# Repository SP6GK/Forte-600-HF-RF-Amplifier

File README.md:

# Forte 600

This is a hardware repository for a 600 W linear RF amplifier working in the 1.8-30 MHz spectrum. I have performed extensive measurements of the output for different configurations of the output transmission line transformers (TLTs). Unfortunately, I don't have the equipment to test this amplifier above 30 MHz, but according to S11 measurements of the output, it should also cover the 6 m band with lower output power.

I recommend using a single 17 Ohm coaxial cable (HF141-17-FEP by Qaxial) for winding the TLTs. However, as shown in my tests, you can use a parallel combination of 50 and 25 Ohm cables, which are easier to find and less expensive. Such an improvised transformer will have worse Power Added Efficiency (PAE) and won't maintain peak power over the maximum wide bandwidth. The ferrite cores used are Fair-Rite 2661102002.

For more details, you can read my paper or full master thesis, which will be published on my webpage in the coming months: [https://www.sp6gk.com/](https://www.sp6gk.com/).

This project was inspired by Razvan Fatu's 600 W amplifier: [A 600W Broadband HF Amplifier Using Affordable LDMOS Devices](https://qrpblog.com/2019/10/a-600w-broadband-hf-amplifier-using-affordable-ldmos-devices/). The goal of this work was to perform measurements of return loss of the input and output matching network, characterize the linearity, power added efficiency (PAE), and most importantly, the impact of "improvised" TLTs over a "textbook" TLT.

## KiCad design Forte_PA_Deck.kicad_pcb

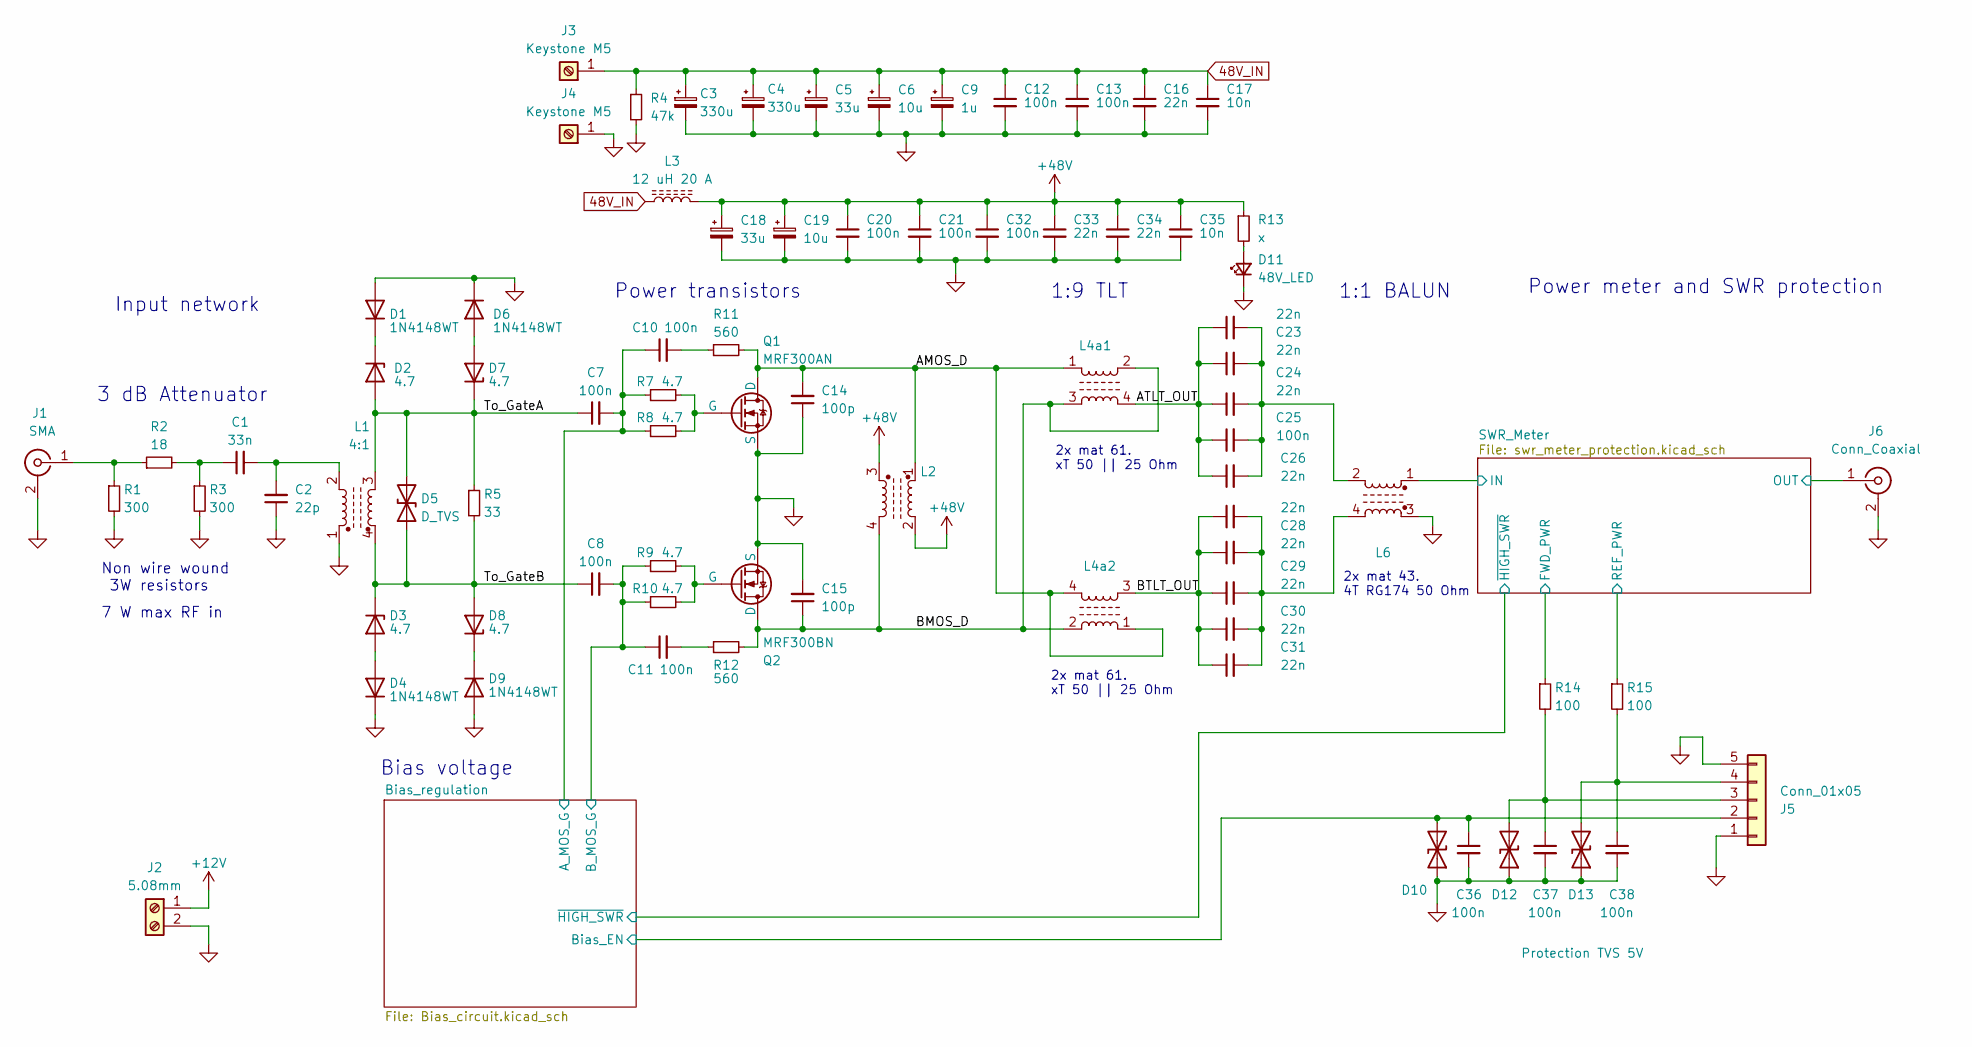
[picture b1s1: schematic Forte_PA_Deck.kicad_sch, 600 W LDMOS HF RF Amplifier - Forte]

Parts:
C1: 33n; C_0805_2012Metric_Pad1.18x1.45mm_HandSolder
C2: 22p; C_0805_2012Metric_Pad1.18x1.45mm_HandSolder
C3, C4: 330u; CP_Elec_18x17.5
C5, C18: 33u; CP_Elec_10x10.5
C6, C19: 10u; CP_Elec_10x10.5
C7, C8: 100n; C_1210_3225Metric_Pad1.33x2.70mm_HandSolder
C9: 1u; C_1206_3216Metric_Pad1.33x1.80mm_HandSolder
C10, C11, C12, C13, C20, C21, C25, C32: 100n; C_1206_3216Metric_Pad1.33x1.80mm_HandSolder
C14, C15: 100p; C_1206_3216Metric_Pad1.33x1.80mm_HandSolder
C16, C22, C23, C24, C26, C27, C28, C29, C30, C31, C33, C34: 22n; C_1206_3216Metric_Pad1.33x1.80mm_HandSolder
C17, C35: 10n; C_1206_3216Metric_Pad1.33x1.80mm_HandSolder
C36, C37, C38: 100n; C_0805_2012Metric_Pad1.18x1.45mm_HandSolder
D1, D4, D6, D9: 1N4148WT; D_SMB
D2, D3, D7, D8: 4.7; D_SMB
D5: D_TVS; D_SMC_Handsoldering
D10: 3.6; D_SMF
D11: 48V_LED; LED_0805_2012Metric_Pad1.15x1.40mm_HandSolder
D12, D13: Protection TVS 5V; D_SMF
J1: SMA; SMA_Amphenol_132134-10_Vertical
J2: 5.08mm; PinSocket_1x02_P2.54mm_Vertical_SMD_Pin1Right
J3, J4: Keystone M5; M5_screw_terminal_Keystone
J5: Conn_01x05; PinHeader_1x05_P2.54mm_Vertical_SMD_Pin1Left
J6: Conn_Coaxial; Coax_connector
L1: 4:1; Binocular_trafo_small
L2: L_Ferrite_Coupled; VDD_Pads
L3: 12 uH 20 A; EMI_inductor
L4a1, L4a2: L_Ferrite_Coupled; TLT_Trafo
L6: 2x mat 43. 4T RG174 50 Ohm; Trafo_623-2661102002
Q1: MRF300AN; TO-247-3_Horizontal_TabDown
Q2: MRF300BN; TO-247-3_Horizontal_TabDown
R1, R3: 300; R_2816_7142Metric_Pad3.20x4.45mm_HandSolder
R2: 18; R_2512_6332Metric_Pad1.40x3.35mm_HandSolder
R4: 47k; C_1206_3216Metric_Pad1.33x1.80mm_HandSolder
R5: 33; R_2512_6332Metric
R7, R8, R9, R10: 4.7; C_1206_3216Metric_Pad1.33x1.80mm_HandSolder
R11, R12: 560; R_2512_6332Metric_Pad1.40x3.35mm_HandSolder
R13: x; R_0805_2012Metric_Pad1.20x1.40mm_HandSolder
R14, R15: 100; R_0603_1608Metric_Pad0.98x0.95mm_HandSolder

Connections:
48V_IN: C3.1, C4.1, C5.1, C6.1, C9.1, C12.1, C13.1, C16.1, C17.1, J3.1, L3.1, R4.1
+12V: J2.1; also elsewhere on the board
+48V: C18.1, C19.1, C20.1, C21.1, C32.1, C33.1, C34.1, C35.1, L2.2, L2.3, L3.2, R13.1
/AMOS_D: C14.2, L2.1, L4a1.1, L4a2.1, L4a2.4, Q1.3 (D), R11.2; also elsewhere on the board
/ATLT_OUT: C22.1, C23.1, C24.1, C25.1, C26.1, L4a1.4; also elsewhere on the board
/BMOS_D: C15.1, L2.4, L4a1.2, L4a1.3, L4a2.2, Q2.1 (D), R12.2; also elsewhere on the board
/BTLT_OUT: C27.1, C28.1, C29.1, C30.1, C31.1, L4a2.3; also elsewhere on the board
/Bias_regulation/A_MOS_G: C7.2, C10.1, R7.1, R8.1; also elsewhere on the board
/Bias_regulation/B_MOS_G: C8.2, C11.1, R9.1, R10.1; also elsewhere on the board
/Bias_regulation/Bias_EN: C36.1, D10.2 (A2), J5.2; also elsewhere on the board
/SWR_Meter/FWD_PWR: R14.1; also elsewhere on the board
/SWR_Meter/IN: L6.1; also elsewhere on the board
/SWR_Meter/OUT: J6.1 (In); also elsewhere on the board
/SWR_Meter/REF_PWR: R15.1; also elsewhere on the board
/To_GateA: C7.1, D2.2 (A), D5.2 (A2), D7.1 (K), L1.3, R5.1
/To_GateB: C8.1, D3.1 (K), D5.1 (A1), D8.2 (A), L1.4, R5.2
GND: C2.1, C3.2, C4.2, C5.2, C6.2, C9.2, C12.2, C13.2, C14.1, C15.2, C16.2, C17.2, C18.2, C19.2, C20.2, C21.2, C32.2, C33.2, C34.2, C35.2, C36.2, C37.2, C38.2, D1.2 (A), D4.1 (K), D6.1 (K), D9.2 (A), D10.1 (A1), D11.1 (K), D12.1 (A1), D13.1 (A1), J1.2 (Ext), J2.2, J4.1, J5.1, J5.5, J6.2 (Ext), L1.1, L6.3, Q1.2 (S), Q2.2 (S), R1.2, R3.2, R4.2; also elsewhere on the board
unnamed: C1.1, R2.2, R3.1
unnamed: C1.2, C2.2, L1.2
unnamed: C10.2, R11.1
unnamed: C11.2, R12.1
unnamed: C22.2, C23.2, C24.2, C25.2, C26.2, L6.2
unnamed: C27.2, C28.2, C29.2, C30.2, C31.2, L6.4
unnamed: D1.1 (K), D2.1 (K)
unnamed: D3.2 (A), D4.2 (A)
unnamed: D6.2 (A), D7.2 (A)
unnamed: D8.1 (K), D9.1 (K)
unnamed: D11.2 (A), R13.2
unnamed: C37.1, D12.2 (A2), J5.3, R14.2
unnamed: C38.1, D13.2 (A2), J5.4, R15.2
unnamed: J1.1 (In), R1.1, R2.1
unnamed: Q1.1 (G), R7.2, R8.2
unnamed: Q2.3 (G), R9.2, R10.2

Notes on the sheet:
Input network
1:1 BALUN
2x mat 61. xT 50 || 25 Ohm
7 W max RF in
Power transistors
1:9 TLT
2x mat 43. 4T RG174 50 Ohm
Power meter and SWR protection
Bias voltage
3 dB Attenuator
Non wire wound 3W resistors

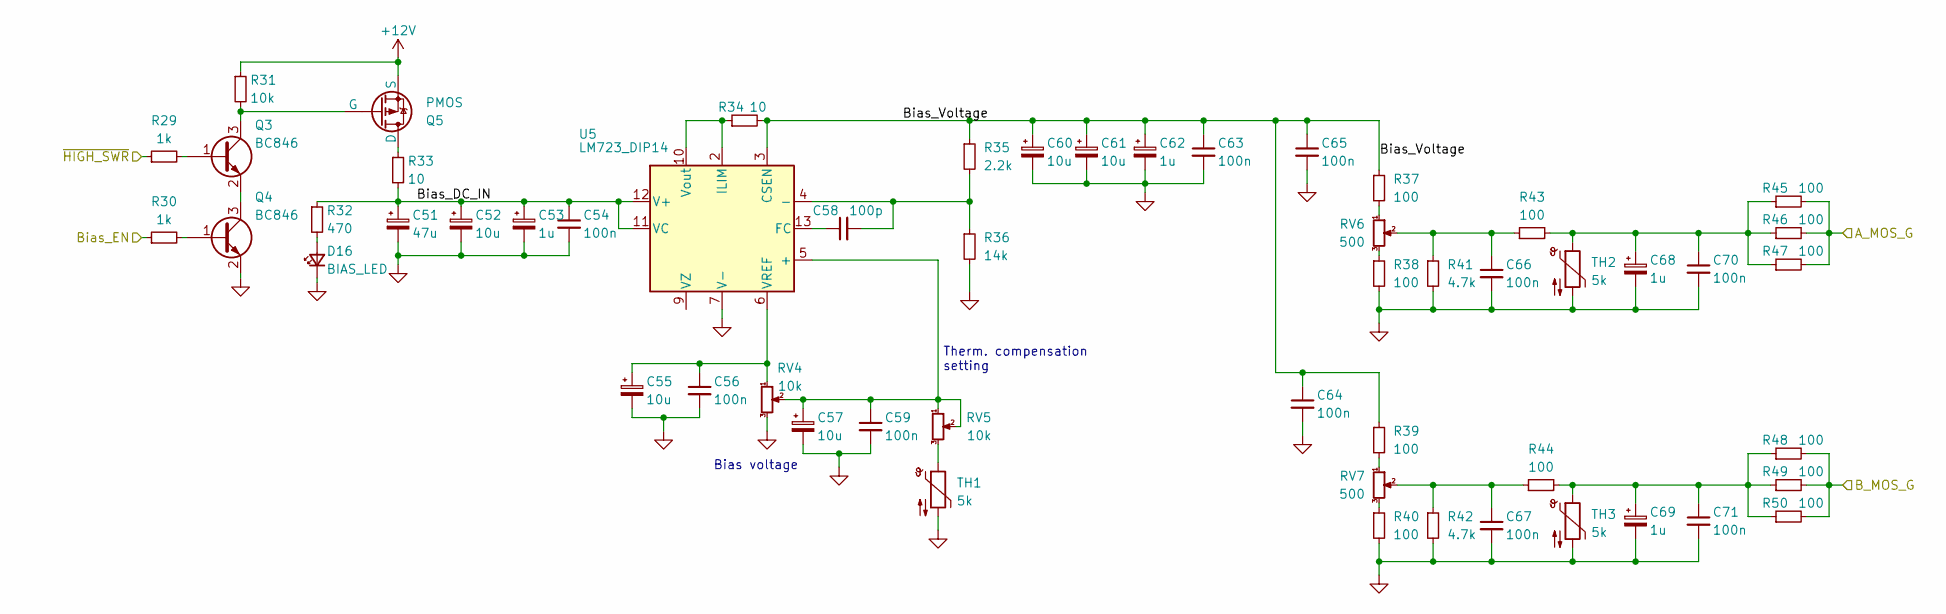
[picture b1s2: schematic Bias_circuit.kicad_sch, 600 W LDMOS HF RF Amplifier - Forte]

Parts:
C51: 47u; CP_Elec_10x10.5
C52, C55, C57, C60, C61: 10u; C_0805_2012Metric_Pad1.18x1.45mm_HandSolder
C53, C62, C68, C69: 1u; C_0805_2012Metric_Pad1.18x1.45mm_HandSolder
C54, C56, C59, C63, C64, C65, C66, C67, C70, C71: 100n; C_0805_2012Metric_Pad1.18x1.45mm_HandSolder
C58: 100p; C_1206_3216Metric_Pad1.33x1.80mm_HandSolder
D16: BIAS_LED; LED_0805_2012Metric_Pad1.15x1.40mm_HandSolder
Q3, Q4: BC846; SOT-23
Q5: PMOS; SOT-23
R29, R30: 1k; R_0603_1608Metric_Pad0.98x0.95mm_HandSolder
R31: 10k; R_0603_1608Metric_Pad0.98x0.95mm_HandSolder
R32: 470; R_0805_2012Metric_Pad1.20x1.40mm_HandSolder
R33, R34: 10; R_0805_2012Metric_Pad1.20x1.40mm_HandSolder
R35: 2.2k; R_0805_2012Metric_Pad1.20x1.40mm_HandSolder
R36: 14k; R_0805_2012Metric_Pad1.20x1.40mm_HandSolder
R37, R38, R39, R40, R43, R44, R45, R46, R47, R48, R49, R50: 100; R_1812_4532Metric_Pad1.30x3.40mm_HandSolder
R41, R42: 4.7k; C_0805_2012Metric_Pad1.18x1.45mm_HandSolder
RV4, RV5: 10k; Potentiometer_Bourns_3269W_Vertical
RV6, RV7: 500; Potentiometer_Bourns_3269W_Vertical
TH1, TH2, TH3: 5k; R_Axial_DIN0207_L6.3mm_D2.5mm_P2.54mm_Vertical
U5: LM723_DIP14; SO-14_3.9x8.65mm_P1.27mm

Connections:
+12V: Q5.2 (S), R31.1; also elsewhere on the board
/Bias_regulation/A_MOS_G: R45.2, R46.2, R47.2; also elsewhere on the board
/Bias_regulation/B_MOS_G: R48.2, R49.2, R50.2; also elsewhere on the board
/Bias_regulation/Bias_DC_IN: C51.1, C52.1, C53.1, C54.1, R32.1, R33.2, U5.11 (VC), U5.12 (V+)
/Bias_regulation/Bias_EN: R30.1; also elsewhere on the board
/Bias_regulation/Bias_Voltage: C60.1, C61.1, C62.1, C63.1, C64.1, C65.1, R34.2, R35.1, R37.1, R39.1, U5.3 (CSEN)
/Bias_regulation/~HIGH_SWR: R29.1; also elsewhere on the board
GND: C51.2, C52.2, C53.2, C54.2, C55.2, C56.2, C57.2, C59.2, C60.2, C61.2, C62.2, C63.2, C64.2, C65.2, C66.2, C67.2, C68.2, C69.2, C70.2, C71.2, D16.1 (K), Q4.2 (E), R36.2, R38.2, R40.2, R41.2, R42.2, RV4.3, TH1.2, TH2.2, TH3.2, U5.7 (V-); also elsewhere on the board
unnamed: C66.1, R41.1, R43.1, RV6.2
unnamed: C67.1, R42.1, R44.1, RV7.2
unnamed: C68.1, C70.1, R43.2, R45.1, R46.1, R47.1, TH2.1
unnamed: C69.1, C71.1, R44.2, R48.1, R49.1, R50.1, TH3.1
unnamed: D16.2 (A), R32.2
unnamed: Q3.1 (B), R29.2
unnamed: Q3.3 (C), Q5.1 (G), R31.2
unnamed: Q3.2 (E), Q4.3 (C)
unnamed: Q4.1 (B), R30.2
unnamed: Q5.3 (D), R33.1
unnamed: R37.2, RV6.1
unnamed: R38.1, RV6.3
unnamed: R39.2, RV7.1
unnamed: R40.1, RV7.3
unnamed: RV5.3, TH1.1
unnamed: C57.1, C59.1, RV4.2, RV5.1, RV5.2, U5.5 (+)
unnamed: C58.2, R35.2, R36.1, U5.4 (-)
unnamed: C58.1, U5.13 (FC)
unnamed: R34.1, U5.2 (ILIM), U5.10 (Vout)
unnamed: C55.1, C56.1, RV4.1, U5.6 (VREF)

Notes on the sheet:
Bias voltage
Therm. compensation setting

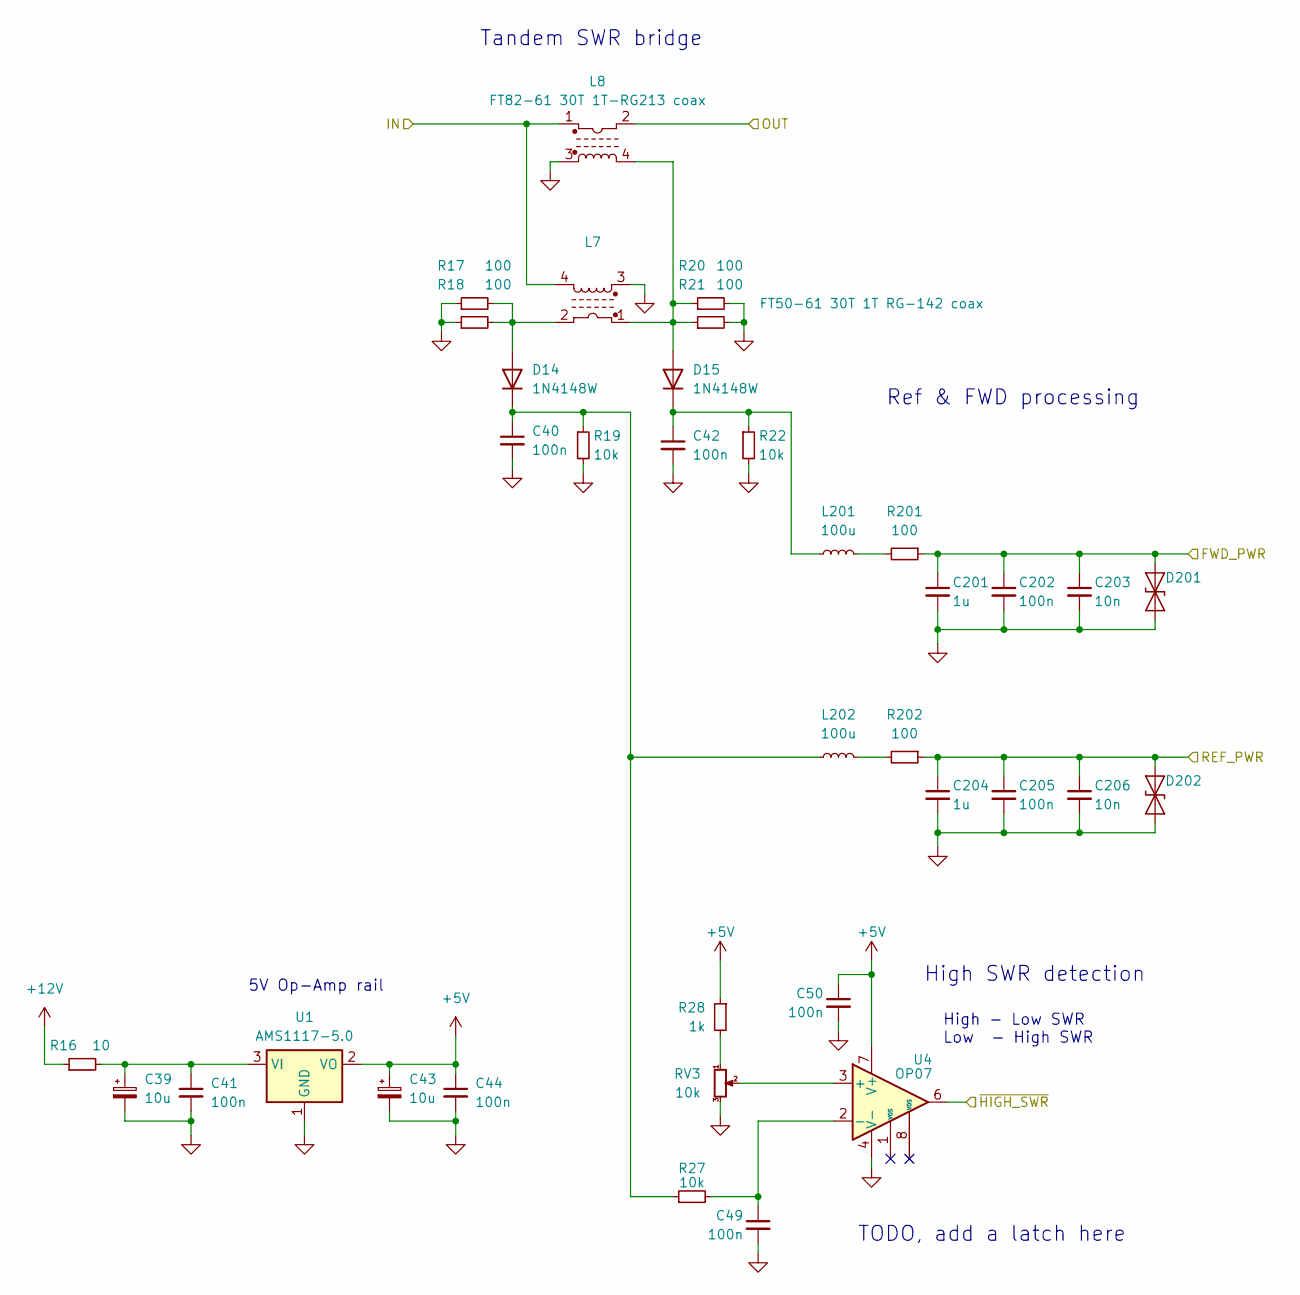
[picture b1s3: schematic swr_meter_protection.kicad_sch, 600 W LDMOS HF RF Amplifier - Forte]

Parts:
C39, C43: 10u; C_0805_2012Metric_Pad1.18x1.45mm_HandSolder
C40, C42: 100n; C_0805_2012Metric_Pad1.18x1.45mm_HandSolder
C41, C44, C49, C50, C202, C205: 100n; C_0603_1608Metric_Pad1.08x0.95mm_HandSolder
C201, C204: 1u; C_0603_1608Metric_Pad1.08x0.95mm_HandSolder
C203, C206: 10n; C_0603_1608Metric_Pad1.08x0.95mm_HandSolder
D14, D15: 1N4148W; D_SMA
D201, D202: SD12_SOD323; D_SOD-323
L7: FT50-61 30T 1T RG-142 coax; FT82_trafo
L8: FT82-61 30T 1T-RG213 coax; FT82_trafo
L201, L202: 100u; L_0805_2012Metric_Pad1.05x1.20mm_HandSolder
R16: 10; R_0805_2012Metric_Pad1.20x1.40mm_HandSolder
R17, R18, R20, R21: 100; R_2010_5025Metric_Pad1.40x2.65mm_HandSolder
R19, R22, R27: 10k; R_0603_1608Metric_Pad0.98x0.95mm_HandSolder
R28: 1k; R_0603_1608Metric_Pad0.98x0.95mm_HandSolder
R201, R202: 100; R_0603_1608Metric_Pad0.98x0.95mm_HandSolder
RV3: 10k; Potentiometer_Bourns_3269W_Vertical
U1: AMS1117-5.0; SOT-223-3_TabPin2
U4: OP07; SOIC-8_3.9x4.9mm_P1.27mm

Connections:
+5V: C43.1, C44.1, C50.1, R28.1, U1.2 (VO), U4.7 (V+)
+12V: R16.1; also elsewhere on the board
/Bias_regulation/~HIGH_SWR: U4.6; also elsewhere on the board
/SWR_Meter/FWD_PWR: C201.1, C202.1, C203.1, D201.1 (A1), R201.1; also elsewhere on the board
/SWR_Meter/IN: L7.4, L8.1; also elsewhere on the board
/SWR_Meter/OUT: L8.2; also elsewhere on the board
/SWR_Meter/REF_PWR: C204.1, C205.1, C206.1, D202.1 (A1), R202.1; also elsewhere on the board
GND: C39.2, C40.2, C41.2, C42.2, C43.2, C44.2, C49.2, C50.2, C201.2, C202.2, C203.2, C204.2, C205.2, C206.2, D201.2 (A2), D202.2 (A2), L7.3, L8.3, R17.1, R18.1, R19.2, R20.2, R21.2, R22.2, RV3.3, U1.1 (GND), U4.4 (V-); also elsewhere on the board
unnamed: D14.2 (A), L7.2, R17.2, R18.2
unnamed: C40.1, D14.1 (K), L202.1, R19.1, R27.1
unnamed: D15.2 (A), L7.1, L8.4, R20.1, R21.1
unnamed: C42.1, D15.1 (K), L201.1, R22.1
unnamed: L201.2, R201.2
unnamed: L202.2, R202.2
unnamed: R28.2, RV3.1
unnamed: C39.1, C41.1, R16.2, U1.3 (VI)
unnamed: RV3.2, U4.3 (+)
unnamed: C49.1, R27.2, U4.2 (-)

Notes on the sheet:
TODO, add a latch here
Ref & FWD processing
Tandem SWR bridge
High SWR detection
High - Low SWR Low - High SWR
5V Op-Amp rail

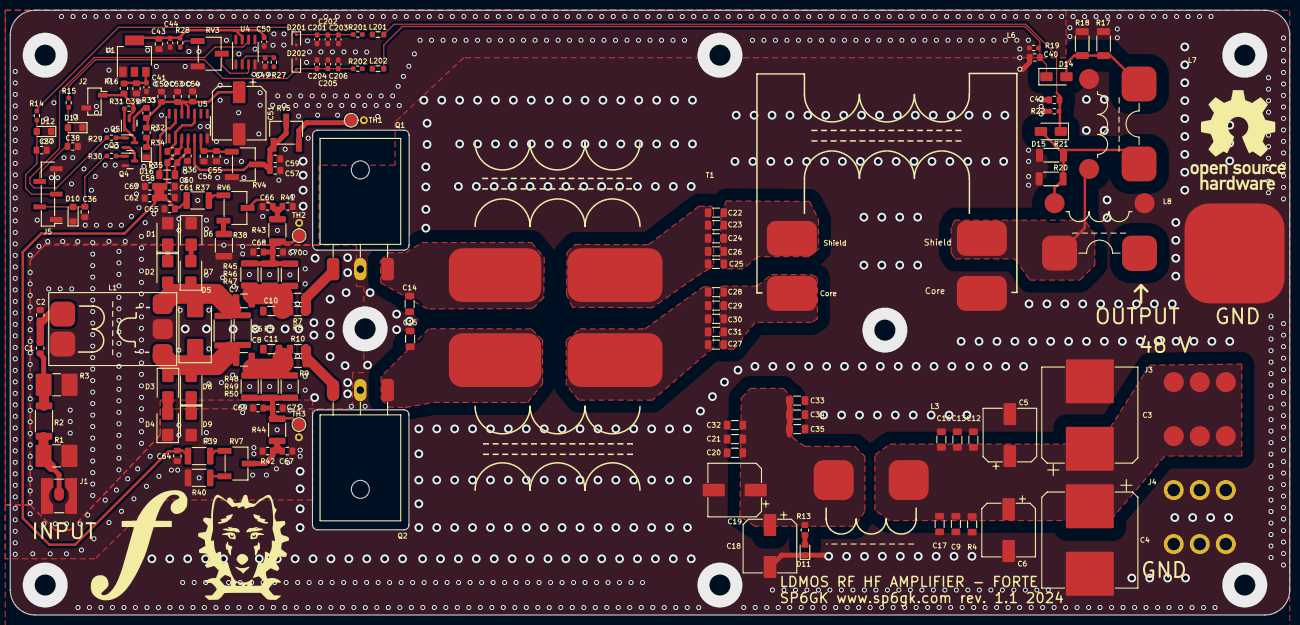
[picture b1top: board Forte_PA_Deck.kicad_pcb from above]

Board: 2 copper layers, 256.0 x 121.0 mm, 167 parts (0 on the bottom side), 65 nets.

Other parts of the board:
R6: 33; R_2512_6332Metric
T1: Transformer_1P_1S; TLT_Trafo

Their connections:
/AMOS_D: T1.1 (AA); also elsewhere on the board
/ATLT_OUT: T1.2; also elsewhere on the board
/BMOS_D: T1.3; also elsewhere on the board
/BTLT_OUT: T1.4; also elsewhere on the board
